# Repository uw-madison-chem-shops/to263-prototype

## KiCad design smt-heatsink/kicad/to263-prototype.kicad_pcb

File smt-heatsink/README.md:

# TO263 prototype with surface mount heatsink

Made to work with Aavid heatsink P/N 573300D00010G

PCB images generated with [tracespace](https://github.com/tracespace/tracespace) follow.

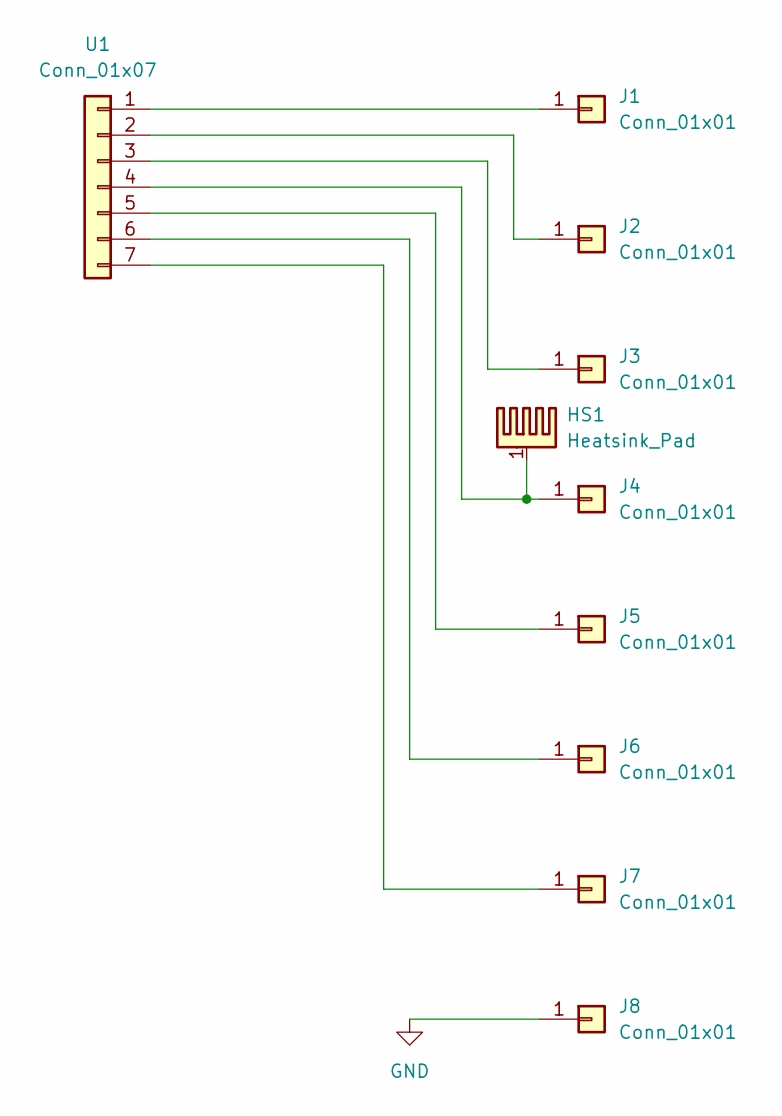
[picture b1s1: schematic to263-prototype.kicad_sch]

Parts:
HS1: Heatsink_Pad; Heatsink_AAVID_573300D00010G_TO-263
J1, J2, J3, J4, J5, J6, J7, J8: Conn_01x01; Banana_Jack_1Pin
U1: Conn_01x07; TO-263-7_TabPin4

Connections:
GND: J8.1
unnamed: J1.1, U1.1
unnamed: J2.1, U1.2
unnamed: J3.1, U1.3
unnamed: HS1.1, J4.1, U1.4
unnamed: J5.1, U1.5
unnamed: J6.1, U1.6
unnamed: J7.1, U1.7

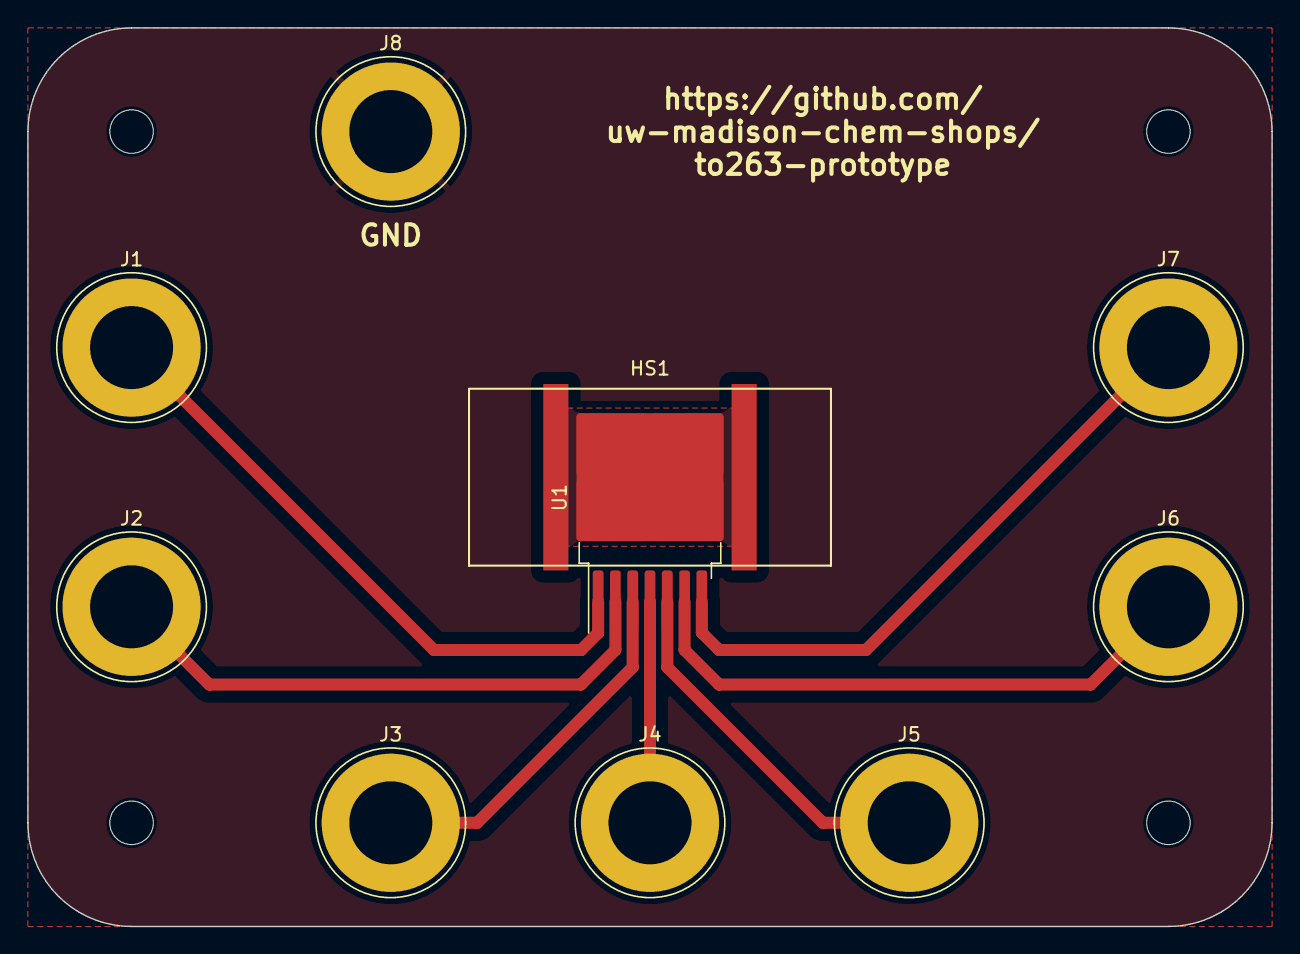
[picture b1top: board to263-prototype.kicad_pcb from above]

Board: 2 copper layers, 91.4 x 66.0 mm, 10 parts (0 on the bottom side), 7 nets.

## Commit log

2023-11-14 jumper gerbers
2023-11-14 drill files
2023-11-14 new svgs
2023-11-14 tht heatsink gerbers
2023-11-14 just via gerbers
2023-11-14 SMT heatsink
